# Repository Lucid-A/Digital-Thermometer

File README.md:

# Digital-Thermometer
2021年暑期工程实践项目：基于STM32F102C6T6芯片的数字温度计设计

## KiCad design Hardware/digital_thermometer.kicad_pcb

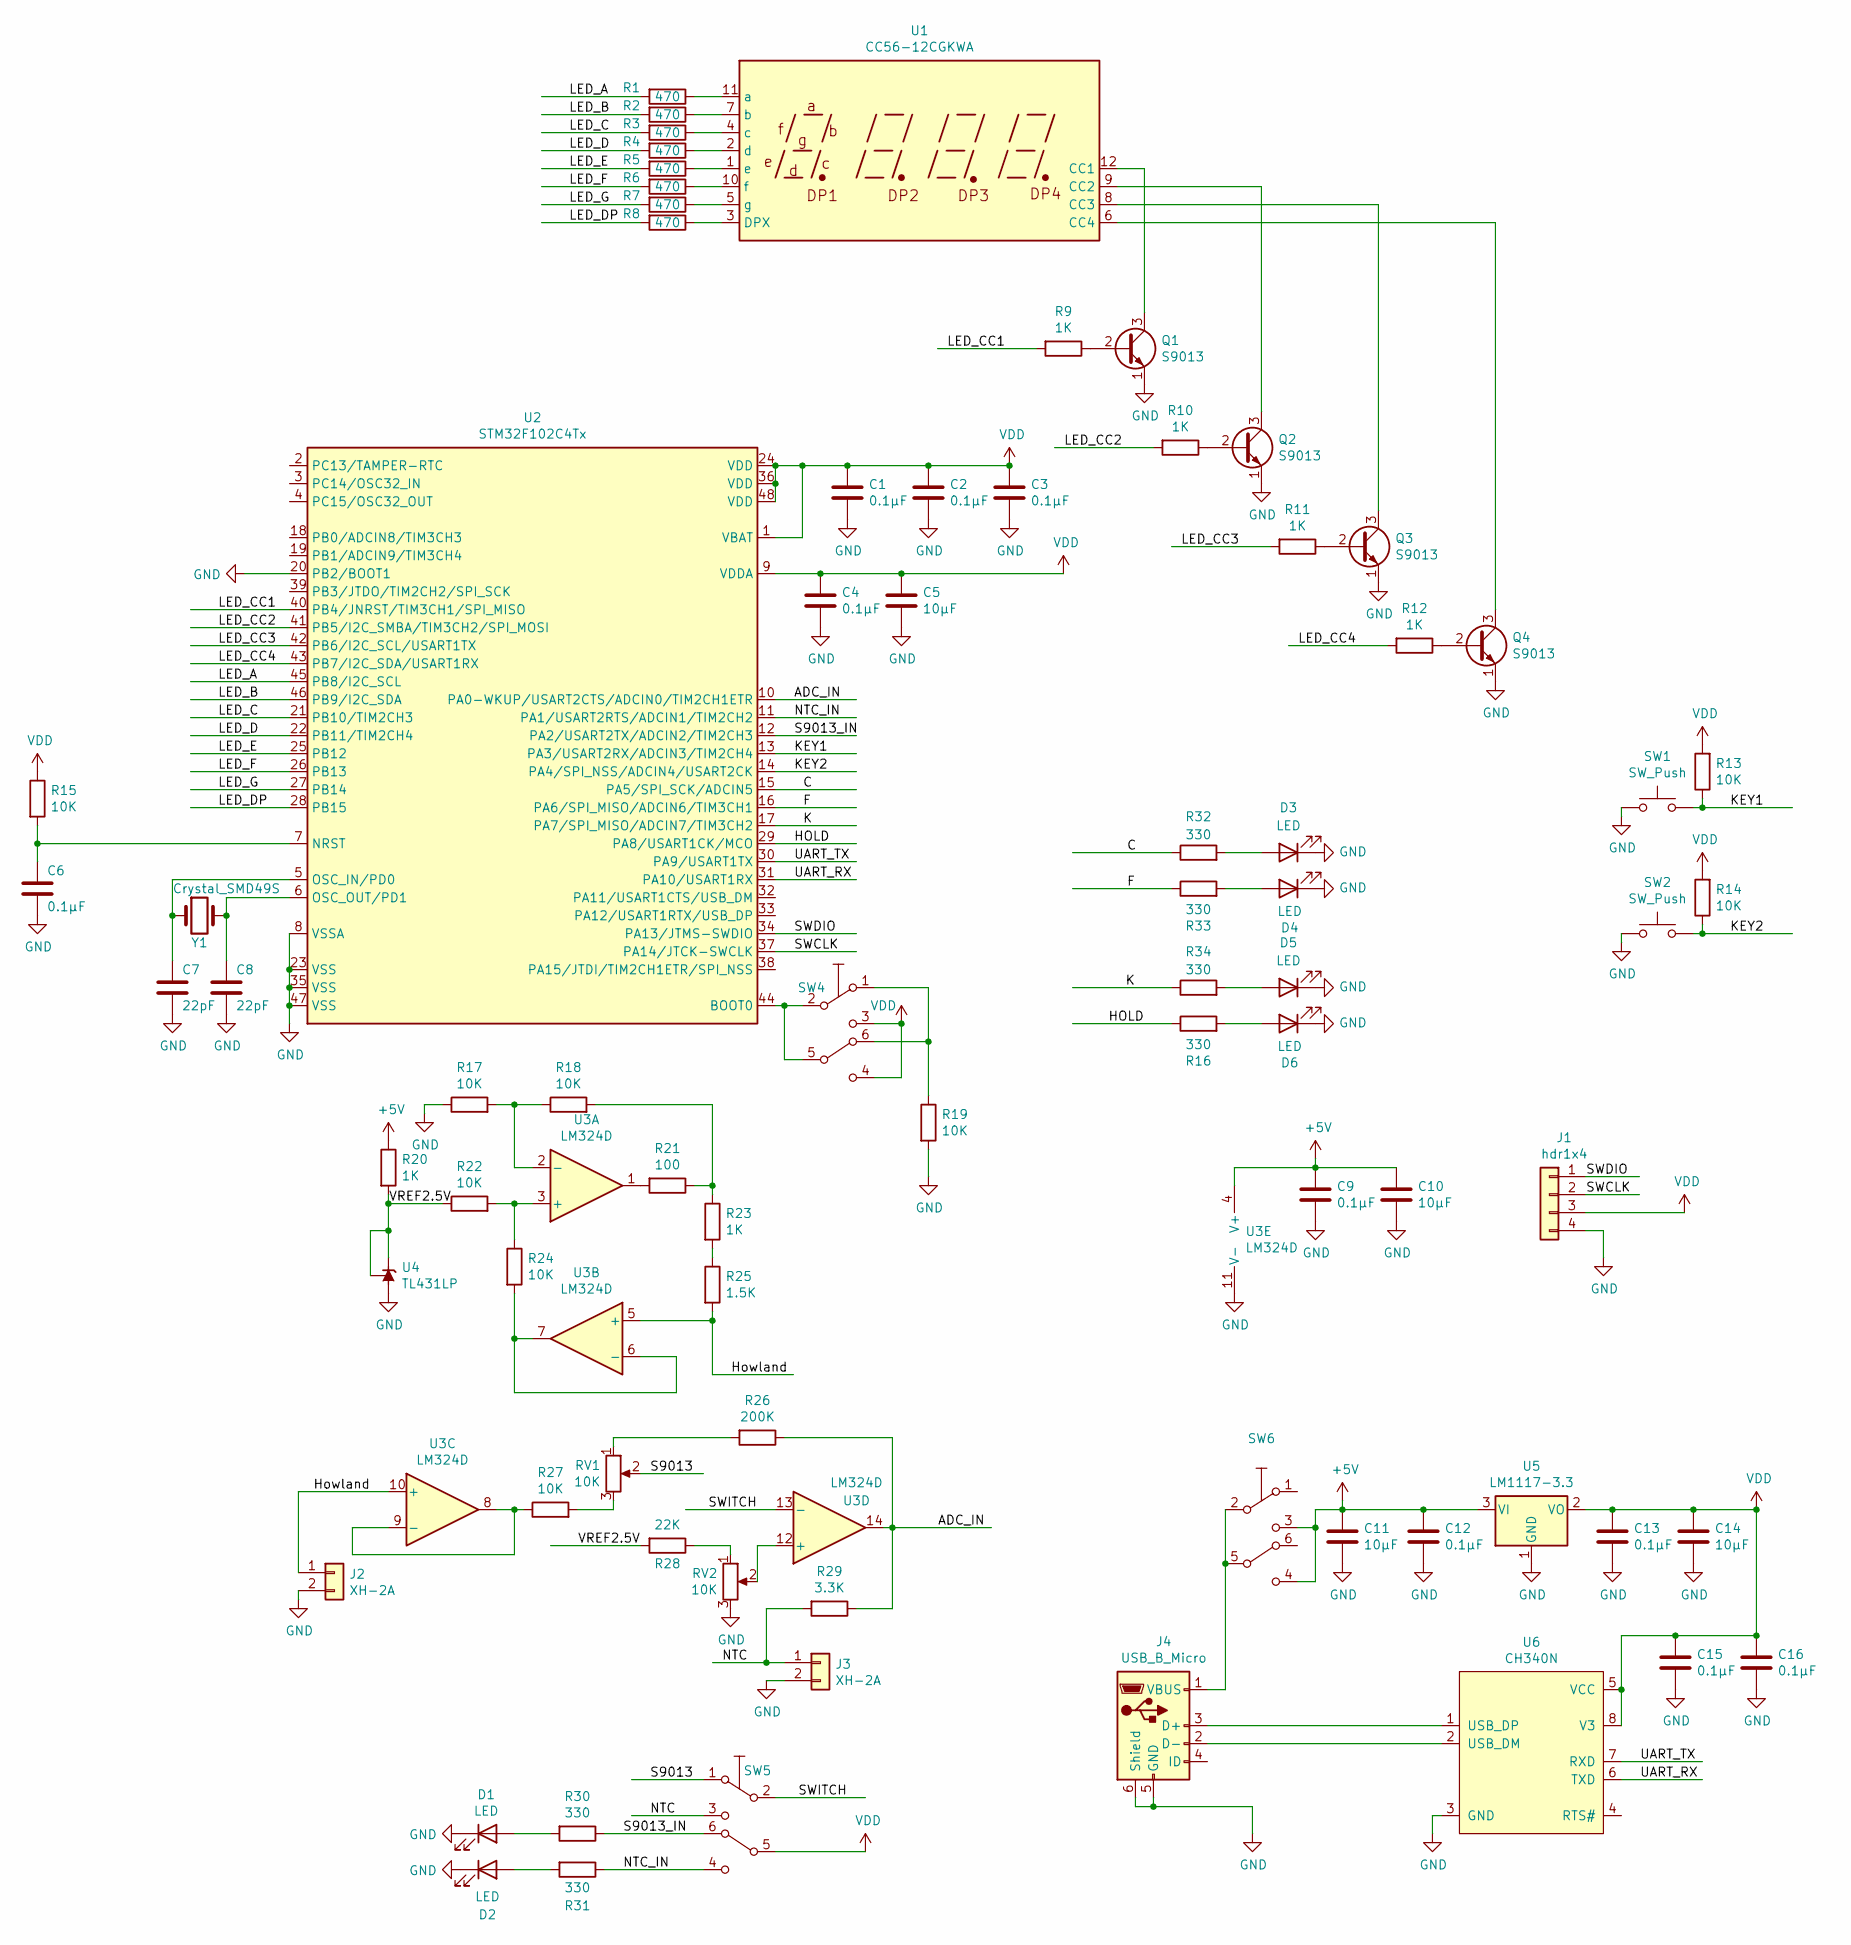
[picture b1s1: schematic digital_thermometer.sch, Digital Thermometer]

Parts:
C1, C2, C3, C4, C6, C9, C12, C13, C15, C16: 0.1μF; C_0805_2012Metric_Pad1.15x1.40mm_HandSolder
C5, C10, C11, C14: 10μF; C_0805_2012Metric_Pad1.15x1.40mm_HandSolder
C7, C8: 22pF; C_0805_2012Metric_Pad1.15x1.40mm_HandSolder
D1, D2, D3, D4, D5, D6: LED; LED_0805_2012Metric
J1: hdr1x4; PinHeader_1x04_P2.54mm_Vertical
J2, J3: XH-2A; JST_XH_B2B-XH-A_1x02_P2.50mm_Vertical
J4: USB_B_Micro; USB_Micro-B_LongPin_6.4mmSnap_Nop
Q1, Q2, Q3, Q4: S9013; TO-92_Inline_Wide
R1, R2, R3, R4, R5, R6, R7, R8: 470; R_0805_2012Metric_Pad1.15x1.40mm_HandSolder
R9, R10, R11, R12, R20, R23: 1K; R_0805_2012Metric_Pad1.15x1.40mm_HandSolder
R13, R14, R15, R17, R18, R19, R22, R24, R27: 10K; R_0805_2012Metric_Pad1.15x1.40mm_HandSolder
R16, R30, R31, R32, R33, R34: 330; R_0805_2012Metric_Pad1.15x1.40mm_HandSolder
R21: 100; R_0805_2012Metric_Pad1.15x1.40mm_HandSolder
R25: 1.5K; R_0805_2012Metric_Pad1.15x1.40mm_HandSolder
R26: 200K; R_0805_2012Metric_Pad1.15x1.40mm_HandSolder
R28: 22K; R_0805_2012Metric_Pad1.15x1.40mm_HandSolder
R29: 3.3K; R_0805_2012Metric_Pad1.15x1.40mm_HandSolder
RV1, RV2: 10K; Potentiometer_Bourns_3296W_Vertical
SW1, SW2: SW_Push; KEY-SMD_L6.2-W3.6-LS8.0
SW4, SW5, SW6: SW_DPDT_PUSHLOCK_5.8x5.8mm
U1: CC56-12CGKWA; CA56-12CGKWA
U2: STM32F102C4Tx; LQFP-48_7x7mm_P0.5mm
U3: LM324D; SOIC-14_3.9x8.7mm_P1.27mm
U4: TL431LP; TO-92_Inline_Wide
U5: LM1117-3.3; SOT-223-3_TabPin2
U6: CH340N; SO-8_3.9x4.9mm_P1.27mm
Y1: Crystal_SMD49S; Crystal_SMD_HC49-SD

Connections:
+5V: C9.1, C10.1, C11.1, C12.1, R20.1, SW6.3 (C), SW6.4 (NO2), U3.4 (V+), U5.3 (VI)
/ADC_IN: R26.1, R29.1, U2.10 (PA0-WKUP/USART2CTS/ADCIN0/TIM2CH1ETR), U3.14
/C: R32.1, U2.15 (PA5/SPI_SCK/ADCIN5)
/F: R33.1, U2.16 (PA6/SPI_MISO/ADCIN6/TIM3CH1)
/HOLD: R16.1, U2.29 (PA8/USART1CK/MCO)
/Howland: J2.1, R25.2, U3.5 (+), U3.10 (+)
/K: R34.1, U2.17 (PA7/SPI_MISO/ADCIN7/TIM3CH2)
/KEY1: R13.1, SW1.2, U2.13 (PA3/USART2RX/ADCIN3/TIM2CH4)
/KEY2: R14.1, SW2.2, U2.14 (PA4/SPI_NSS/ADCIN4/USART2CK)
/LED_A: R1.2, U2.45 (PB8/I2C_SCL)
/LED_B: R2.2, U2.46 (PB9/I2C_SDA)
/LED_C: R3.2, U2.21 (PB10/TIM2CH3)
/LED_CC1: R9.2, U2.40 (PB4/JNRST/TIM3CH1/SPI_MISO)
/LED_CC2: R10.2, U2.41 (PB5/I2C_SMBA/TIM3CH2/SPI_MOSI)
/LED_CC3: R11.2, U2.42 (PB6/I2C_SCL/USART1TX)
/LED_CC4: R12.2, U2.43 (PB7/I2C_SDA/USART1RX)
/LED_D: R4.2, U2.22 (PB11/TIM2CH4)
/LED_DP: R8.2, U2.28 (PB15)
/LED_E: R5.2, U2.25 (PB12)
/LED_F: R6.2, U2.26 (PB13)
/LED_G: R7.2, U2.27 (PB14)
/NTC: J3.1, R29.2, SW5.3 (C)
/NTC_IN: R31.1, SW5.4 (NO2), U2.11 (PA1/USART2RTS/ADCIN1/TIM2CH2)
/S9013: RV1.2, SW5.1 (A)
/S9013_IN: R30.1, SW5.6 (NC2), U2.12 (PA2/USART2TX/ADCIN2/TIM2CH3)
/SWCLK: J1.2, U2.37 (PA14/JTCK-SWCLK)
/SWDIO: J1.1, U2.34 (PA13/JTMS-SWDIO)
/SWITCH: SW5.2 (COM1), U3.13 (-)
/UART_RX: U2.31 (PA10/USART1RX), U6.6 (TXD)
/UART_TX: U2.30 (PA9/USART1TX), U6.7 (RXD)
/VREF2.5V: R20.2, R22.1, R28.2, U4.1 (REF), U4.3 (K)
GND: C1.2, C2.2, C3.2, C4.2, C5.2, C6.2, C7.2, C8.2, C9.2, C10.2, C11.2, C12.2, C13.2, C14.2, C15.2, C16.2, D1.1 (K), D2.1 (K), D3.1 (K), D4.1 (K), D5.1 (K), D6.1 (K), J1.4, J2.2, J3.2, J4.5 (GND), J4.6 (Shield), Q1.1 (E), Q2.1 (E), Q3.1 (E), Q4.1 (E), R17.1, R19.2, RV2.3, SW1.1, SW2.1, U2.8 (VSSA), U2.20 (PB2/BOOT1), U2.23 (VSS), U2.35 (VSS), U2.47 (VSS), U3.11 (V-), U4.2 (A), U5.1 (GND), U6.3 (GND)
unnamed: C6.1, R15.2, U2.7 (NRST)
unnamed: C7.1, U2.5 (OSC_IN/PD0), Y1.1
unnamed: C8.1, U2.6 (OSC_OUT/PD1), Y1.2
unnamed: D1.2 (A), R30.2
unnamed: D2.2 (A), R31.2
unnamed: D3.2 (A), R32.2
unnamed: D4.2 (A), R33.2
unnamed: D5.2 (A), R34.2
unnamed: D6.2 (A), R16.2
unnamed: J4.1 (VBUS), SW6.2 (COM1), SW6.5 (COM2)
unnamed: J4.2 (D-), U6.2 (USB_DM)
unnamed: J4.3 (D+), U6.1 (USB_DP)
unnamed: Q1.2 (B), R9.1
unnamed: Q1.3 (C), U1.12 (CC1)
unnamed: Q2.2 (B), R10.1
unnamed: Q2.3 (C), U1.9 (CC2)
unnamed: Q3.2 (B), R11.1
unnamed: Q3.3 (C), U1.8 (CC3)
unnamed: Q4.2 (B), R12.1
unnamed: Q4.3 (C), U1.6 (CC4)
unnamed: R1.1, U1.11 (a)
unnamed: R2.1, U1.7 (b)
unnamed: R3.1, U1.4 (c)
unnamed: R4.1, U1.2 (d)
unnamed: R5.1, U1.1 (e)
unnamed: R6.1, U1.10 (f)
unnamed: R7.1, U1.5 (g)
unnamed: R8.1, U1.3 (DPX)
unnamed: R17.2, R18.1, U3.2 (-)
unnamed: R18.2, R21.1, R23.1
unnamed: R19.1, SW4.1 (A), SW4.6 (NC2)
unnamed: R21.2, U3.1
unnamed: R22.2, R24.1, U3.3 (+)
unnamed: R23.2, R25.1
unnamed: R24.2, U3.6 (-), U3.7
unnamed: R26.2, RV1.1
unnamed: R27.1, U3.8, U3.9 (-)
unnamed: R27.2, RV1.3
unnamed: R28.1, RV2.1
unnamed: RV2.2, U3.12 (+)
unnamed: SW4.2 (COM1), SW4.5 (COM2), U2.44 (BOOT0)
VDD: C1.1, C2.1, C3.1, C4.1, C5.1, C13.1, C14.1, C15.1, C16.1, J1.3, R13.2, R14.2, R15.1, SW4.3 (C), SW4.4 (NO2), SW5.5 (COM2), U2.1 (VBAT), U2.9 (VDDA), U2.24 (VDD), U2.36 (VDD), U2.48 (VDD), U5.2 (VO), U6.5 (VCC), U6.8 (V3)

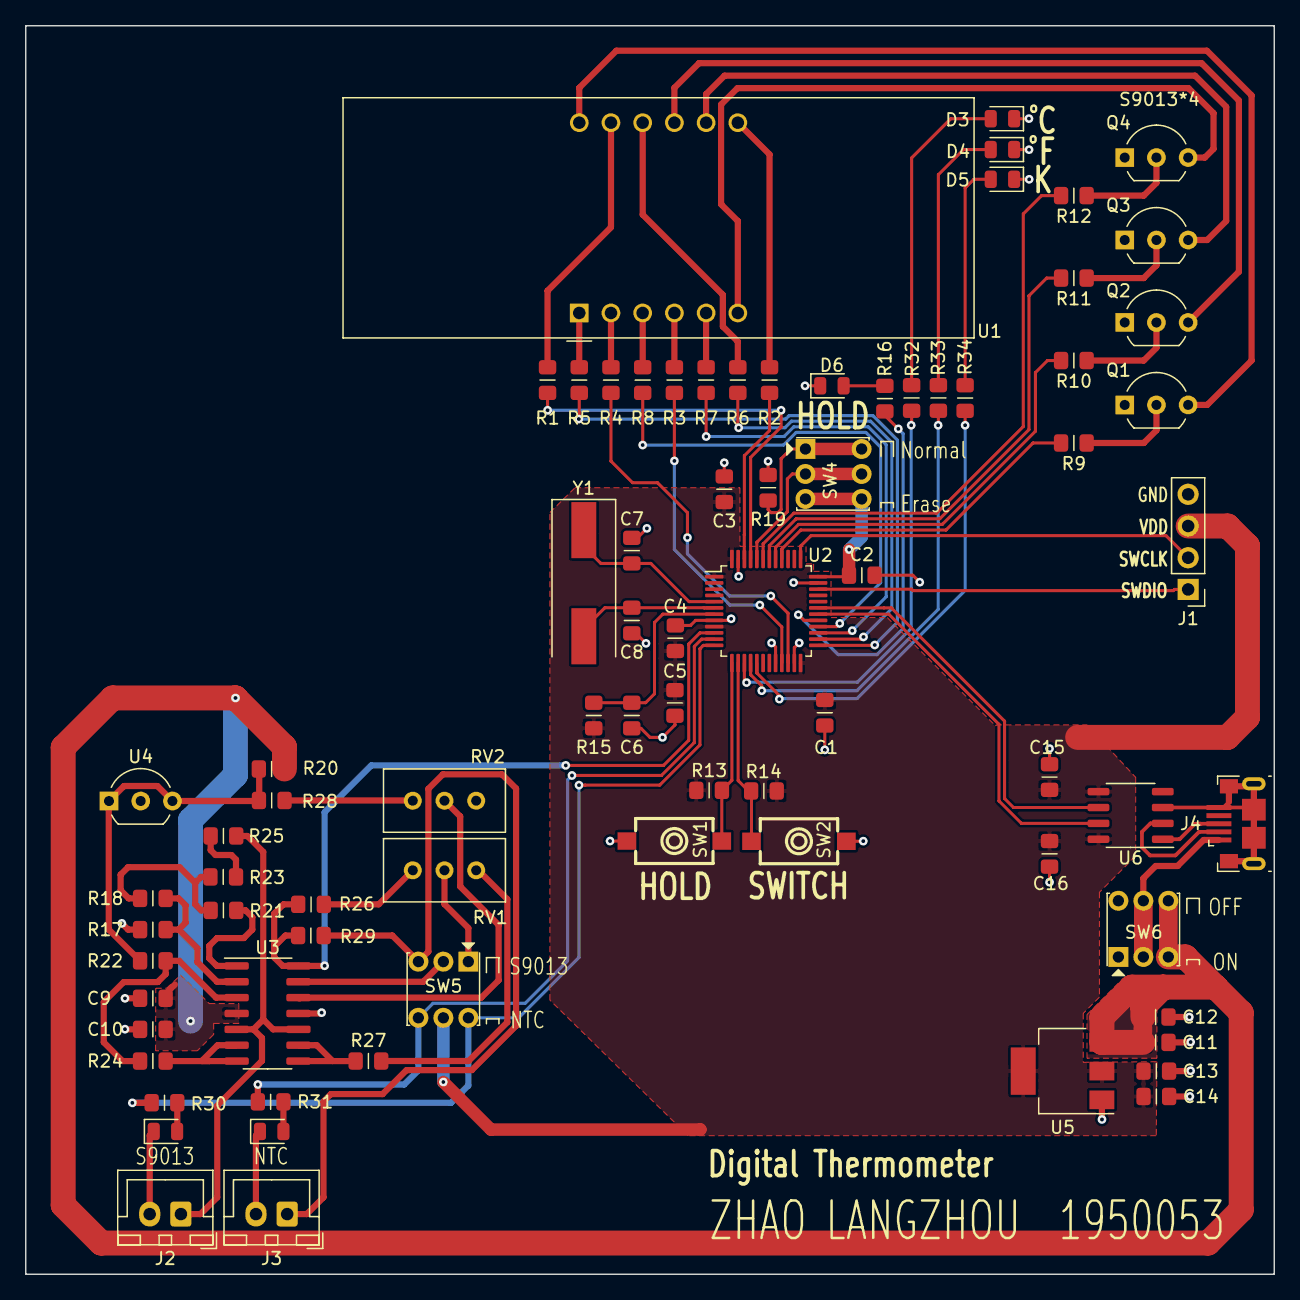
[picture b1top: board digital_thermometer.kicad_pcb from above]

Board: 2 copper layers, 100.0 x 100.0 mm, 78 parts (0 on the bottom side), 74 nets.

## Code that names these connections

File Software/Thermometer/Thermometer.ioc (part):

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Mcu.Name=STM32F102C(4-6)Tx
Mcu.Package=LQFP48
Mcu.UserName=STM32F102C6Tx
PA0-WKUP.Signal=ADCx_IN0
PA1.GPIOParameters=GPIO_Label
PA1.GPIO_Label=NTC
PA1.Signal=GPIO_Input
PA10.Mode=Asynchronous
PA10.Signal=USART1_RX
PA13.Mode=Serial_Wire
PA13.Signal=SYS_JTMS-SWDIO
PA14.Mode=Serial_Wire
PA14.Signal=SYS_JTCK-SWCLK
PA2.GPIOParameters=GPIO_Label
PA2.GPIO_Label=S9013
PA2.Signal=GPIO_Input
PA3.GPIOParameters=GPIO_Label
PA3.GPIO_Label=KEY_HOLD
PA3.Signal=GPIO_Input
PA4.GPIOParameters=GPIO_Label
PA4.GPIO_Label=KEY_SWITCH
PA4.Signal=GPIO_Input
PA5.GPIOParameters=GPIO_Label
PA5.GPIO_Label=LED_C
PA5.Signal=GPIO_Output
PA6.GPIOParameters=GPIO_Label
PA6.GPIO_Label=LED_F
PA6.Signal=GPIO_Output
PA7.GPIOParameters=GPIO_Label
PA7.GPIO_Label=LED_K
PA7.Signal=GPIO_Output
PA8.GPIOParameters=GPIO_Label
PA8.GPIO_Label=HOLD
PA8.Signal=GPIO_Output
PA9.Mode=Asynchronous
PA9.Signal=USART1_TX
PB10.GPIOParameters=GPIO_Label
PB10.GPIO_Label=C
PB10.Signal=GPIO_Output
PB11.GPIOParameters=GPIO_Label
PB11.GPIO_Label=D
PB11.Signal=GPIO_Output
PB12.GPIOParameters=GPIO_Label
PB12.GPIO_Label=E
PB12.Signal=GPIO_Output
PB13.GPIOParameters=GPIO_Label
PB13.GPIO_Label=F
PB13.Signal=GPIO_Output
PB14.GPIOParameters=GPIO_Label
PB14.GPIO_Label=G
PB14.Signal=GPIO_Output
PB15.GPIOParameters=GPIO_Label
PB15.GPIO_Label=DP
PB15.Signal=GPIO_Output
PB4.GPIOParameters=GPIO_Label
PB4.GPIO_Label=CC1
PB4.Signal=GPIO_Output
PB5.GPIOParameters=GPIO_Label
PB5.GPIO_Label=CC2
PB5.Signal=GPIO_Output
PB6.GPIOParameters=GPIO_Label
PB6.GPIO_Label=CC3
PB6.Signal=GPIO_Output
PB7.GPIOParameters=GPIO_Label
PB7.GPIO_Label=CC4
PB7.Signal=GPIO_Output
PB8.GPIOParameters=GPIO_Label
PB8.GPIO_Label=A
PB8.Signal=GPIO_Output
PB9.GPIOParameters=GPIO_Label
PB9.GPIO_Label=B
PB9.Signal=GPIO_Output
PD0-OSC_IN.Mode=HSE-External-Oscillator
PD0-OSC_IN.Signal=RCC_OSC_IN
PD1-OSC_OUT.Mode=HSE-External-Oscillator
PD1-OSC_OUT.Signal=RCC_OSC_OUT
RCC.SYSCLKFreq_VALUE=48000000
RCC.SYSCLKSource=RCC_SYSCLKSOURCE_PLLCLK
board=custom

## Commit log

2021-09-11 add Hardware Designs and Simulations
2021-09-12 v1 with EXTI
2021-09-13 Set footprint config and Generate codes
2021-09-15 add UI
2021-09-15 add Data.xlsx
